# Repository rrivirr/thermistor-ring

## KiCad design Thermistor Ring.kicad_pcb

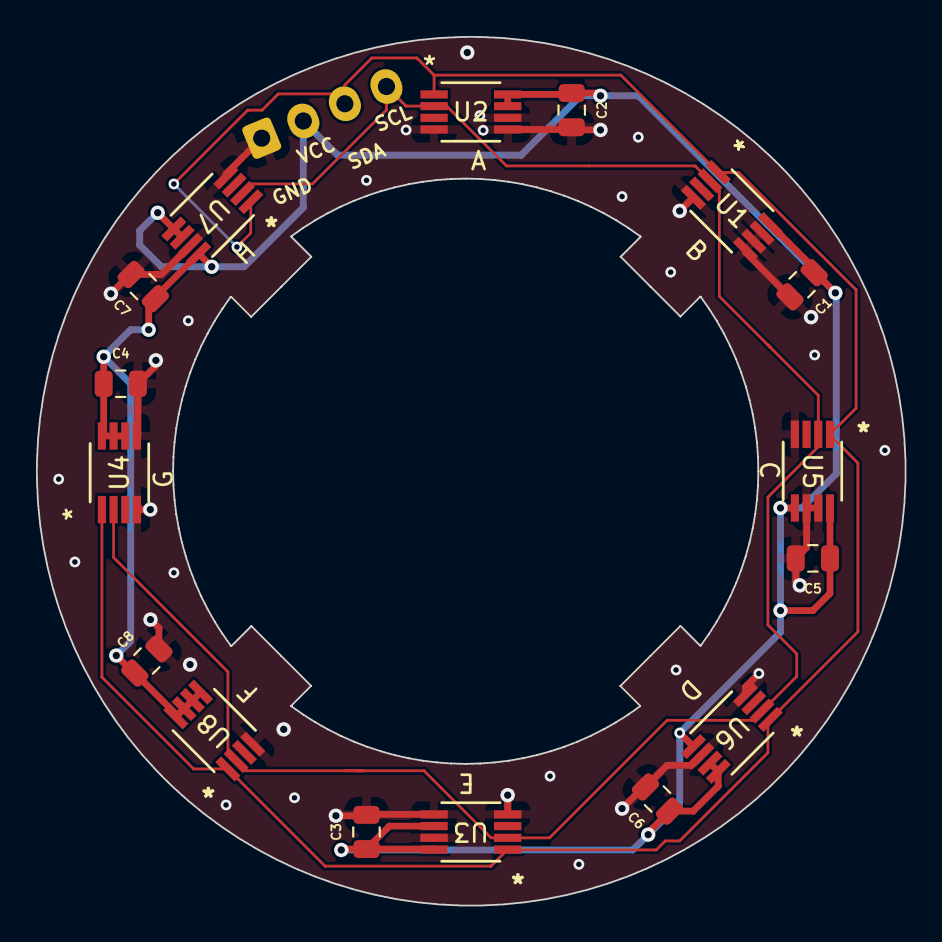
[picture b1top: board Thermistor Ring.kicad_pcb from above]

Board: 2 copper layers, 48.3 x 48.3 mm, 17 parts (1 on the bottom side), 4 nets.

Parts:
C1, C2, C3, C4, C5, C6, C7, C8: 0.1uF; C_0805_2012Metric
J1: Conn_01x04_Socket; JST_XH_B4B-XH-A_1x04_P2.50mm_Vertical
U1, U2, U3, U4, U5, U6, U7, U8: MCP9808T-E/MC; MSOP8_MC_MCH

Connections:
/SCL: J1.4, U1.2 (SCL), U2.2 (SCL), U3.2 (SCL), U4.2 (SCL), U5.2 (SCL), U6.2 (SCL), U7.2 (SCL), U8.2 (SCL)
/SDA: J1.3, U1.1 (SDA), U2.1 (SDA), U3.1 (SDA), U4.1 (SDA), U5.1 (SDA), U6.1 (SDA), U7.1 (SDA), U8.1 (SDA)
GND: C1.2, C2.2, C3.2, C4.2, C5.2, C6.2, C7.2, C8.2, J1.1, U1.4 (GND), U1.5 (A2), U1.6 (A1), U1.7 (A0), U2.4 (GND), U2.5 (A2), U2.6 (A1), U3.4 (GND), U3.5 (A2), U3.7 (A0), U4.4 (GND), U4.5 (A2), U5.4 (GND), U5.6 (A1), U5.7 (A0), U6.4 (GND), U6.6 (A1), U7.4 (GND), U7.7 (A0), U8.4 (GND)
VCC: C1.1, C2.1, C3.1, C4.1, C5.1, C6.1, C7.1, C8.1, J1.2, U1.8 (VDD), U2.7 (A0), U2.8 (VDD), U3.6 (A1), U3.8 (VDD), U4.6 (A1), U4.7 (A0), U4.8 (VDD), U5.5 (A2), U5.8 (VDD), U6.5 (A2), U6.7 (A0), U6.8 (VDD), U7.5 (A2), U7.6 (A1), U7.8 (VDD), U8.5 (A2), U8.6 (A1), U8.7 (A0), U8.8 (VDD)

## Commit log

2023-12-13 first thermistor ring schematic
2023-12-13 footprints added to schematic
2023-12-14 pcb in progress
2023-12-23 saving before moving thermistors
2023-12-26 v0.1 alpha for review
2024-01-11 wip: work on castellated miniboard
2024-01-11 wip: castellated miniboard
2024-01-11 castellated miniboard v1
2024-01-11 layout for manufacturing
2024-01-12 wip: flawed initial array layout attempt
2024-01-12 castellated temp board, updated footprint, array layout
2024-01-24 changing to smaller diameter
2024-01-31 schematic updated for MCP9808 temperature sensor
2024-03-06 shrinking ring
2024-03-10 smaller ring first draft
2024-03-12 wip: some fixes
2024-03-15 Update PCB and resolve DRC
2024-03-28 Pass DRC and fix fills
2024-03-28 Addedtabs for potting
2024-03-28 Cleanup
2024-04-04 Add fiducials
2024-04-04 Clean up
2024-04-04 Fixed fiducial silkscreen
2024-06-05 Reduce size of epad, improve layout
2024-07-09 Change to MSOP thermistor
2024-07-13 Tweaks to updated stencil
2024-10-09 updating pads
2024-10-22 Ouptut adjustments
2024-10-25 Add library for address translator
2024-10-25 Add footprints for MCP9808 MSOP
2024-10-25 Update gitignore
2024-10-25 90% pad size
2025-01-06 adding protcols folder
2025-01-14 moving documentation to the groundwater simulating repo
2025-01-30 wip: messing around with 8 sensors plus i2c translator
2025-10-03 Updated PCB for 8 thermistors
2025-10-10 Update layout
2025-10-24 Fixed layout issues in V2.0
2025-10-28 Updated traces and silkscreen
2026-01-12 fixing solder paste stencil size
2026-02-02 first version of mosfet PWM circuit
